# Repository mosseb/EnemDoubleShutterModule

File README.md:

# EnemDoubleShutterModule
Nodemcu/Homie module for dealing with 1 or 2 shutters with EnemButtons

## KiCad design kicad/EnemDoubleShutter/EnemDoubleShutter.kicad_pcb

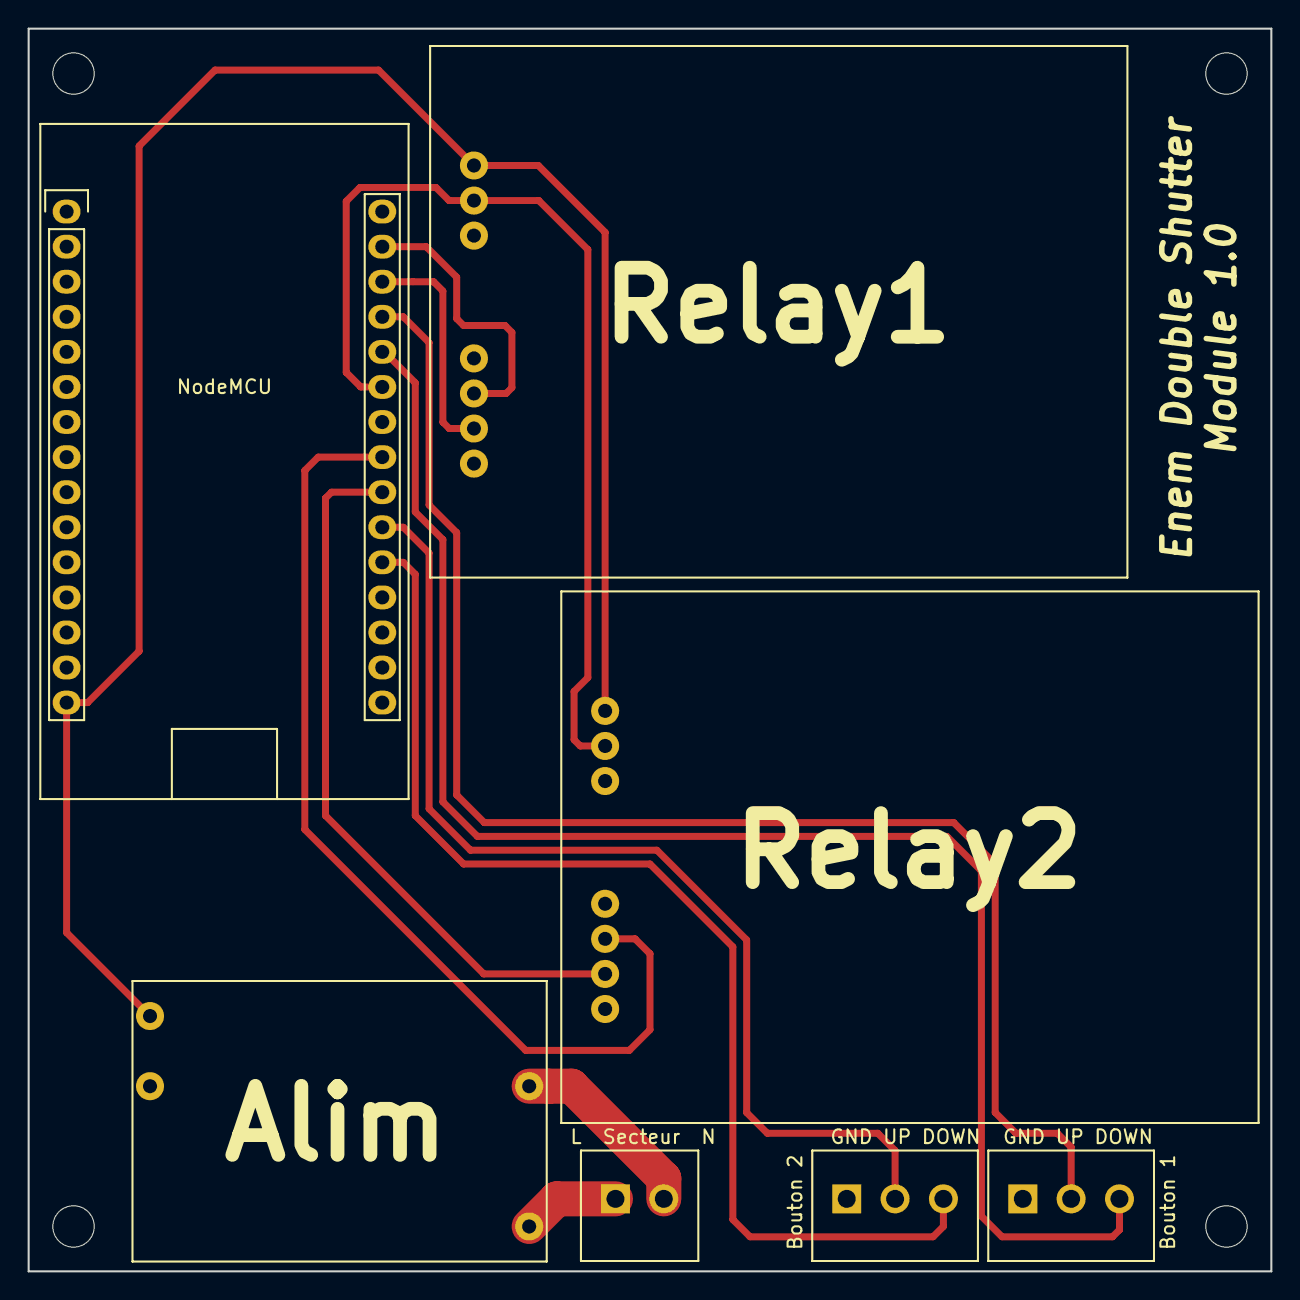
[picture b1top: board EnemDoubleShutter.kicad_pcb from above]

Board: 2 copper layers, 90.0 x 90.0 mm, 7 parts (0 on the bottom side), 13 nets.

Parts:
Alim: Alim; ModuleAlim
Bouton 1: Bouton 1; Bornier3
Bouton 2: Bouton 2; Bornier3
L  Secteur  N: Secteur; Bornier2
NodeMCU: NodeMCU_Amica_R2; NodeMCU_simple
Relay1, Relay2: 2RelaysModule; relayModule

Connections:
+3V3: NodeMCU.25, Relay1.2, Relay2.2
+5V: Alim.3, NodeMCU.15, Relay1.3, Relay2.3
GND: Alim.4, Bouton 1.1, Bouton 2.1, NodeMCU.14, NodeMCU.17, NodeMCU.24, Relay1.1, Relay2.1
unnamed: Alim.1, L Secteur N.1
unnamed: Alim.2, L Secteur N.2
unnamed: Bouton 1.2, NodeMCU.27
unnamed: Bouton 1.3, NodeMCU.26
unnamed: Bouton 2.2, NodeMCU.21
unnamed: Bouton 2.3, NodeMCU.20
unnamed: NodeMCU.29, Relay1.4
unnamed: NodeMCU.28, Relay1.5
unnamed: NodeMCU.23, Relay2.4
unnamed: NodeMCU.22, Relay2.5

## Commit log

2018-03-25 init
2018-03-29 first version
2018-03-29 test
2018-03-29 Add relays logic
2018-04-02 IMplémentation partielle issue #1
2018-04-08 Finish #1
2018-05-01 Add kicad
2018-05-01 ignore local data folder
2018-05-01 Ajout des chemins relatifs au bibliothèques
2018-05-02 Modifications légères sur les pistes. Ajout des noms des GPIO au niveau des boutons et déplacement du nom des boutons. Correction sur le commentaire arrière.
2018-05-06 Corrections et finalisation PCB
2018-05-06 Ajout doc sur schéma + connection volets
2018-05-06 Mise à jour des pins (in & out) suite à la création du PCB.
